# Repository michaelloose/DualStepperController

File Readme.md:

Stepper Controller
==================

Dieses Projekt entstand als kleines Nebenprojekt im Rahmen meiner Masterarbeit und soll eine performante und einfach anzusteuernde Möglichkeit bieten zwei Schrittmotoren mithilfe eines Schrittmotortreibers wie dem DM542 zu betreiben.

||
|:-------------------------------------------------:|:---------------------------------------------------------:
|Bestückte Leiterplatte                             |Beispielhafter Aufbau                                                    

## Befehlsübersicht

Die Übertragung findet
über einen mittels USB-CDC emulierten COM-Port statt. Aus diesem
Grund sind sämtliche Einstellungen zu Baudrate, Daten/Stopbits oder
Paritätsbits hinfällig. Der Controller unterscheidet bei den Befehlen
nicht zwischen Groß- und Kleinschreibung. Das Ende eines Befehles wird
durch ein Carriage Return `<CR> Hex:0x0D` signalisiert. Alternativ wird
auch ein Line Feed `<LF> Hex:0x0A` akzeptiert. Ein Befehl darf eine
maximale Länge von zwölf ASCII-Zeichen zuzüglich des Terminatorzeichens
aufweisen. Wird diese Länge überschritten, so wird das dreizehnte
Zeichen unabhängig vom Inhalt aus Terminator gewertet.\
Zum Testen des Controllers wird eine serielle Konsole benötigt. Dazu
eignet sich die Software *hTerm*, welche sowohl unter Windows
als auch unter Linux ausgeführt werden kann. Um den Motortreiber in eine
Softwareumgebung einzubinden, wurde eine
Treiberklasse in Python entwickelt, die es einem ermöglicht
Steuerbefehle auf einem hohen Level zu senden. Zusätzlich zu dieser
Treiberklasse existiert ebenfalls eine GUI um die Antriebe komfortabel manuell
verfahren zu können.

### Allgemeine Befehle

  |Name               |Befehl     |Erklärung
  |-------------------|-----------|-----------------------------------------------------------------------------------------------------------------------------------------------------
  |Reset              |`RST<cr>`  |Neustart des Controllers. Trennt ebenfalls die USB-Verbindung.
  |Halt               |`HLT<cr>`  |Anhalten aller Antriebe. Neue Befehle werden akzeptiert, Spulen sind weiterhin bestromt.
  |Not-Halt           |`EST<cr>`  |Anhalten aller Antriebe. Neue Befehle werden nicht mehr akzeptiert, Spulenstrom wird abgeschaltet, somit können die Antriebe von Hand bewegt werden
  |Freigabe Not-Halt  |`ESR<cr>`  |Rücksetzen des Not-Halt Zustandes. Spulenstrom wird aktiviert und neue Befehle akzeptiert.

### Steuerbefehle

#### Steuerbefehle an den Controller
 | Byte    |Erlaubte Werte                                | Erklärung
 | ------- |----------------------------------------------| -------------------------------------------------
 | 1       |`A` Antrieb A (Hier Drehtisch)                | Antrieb
 |         |`B` Antrieb B (Hier Linearantrieb)            | 
 | 2       |`P` Position                                  | Art des Befehls
 |         |`S` Geschwindigkeit                           | 
 |         |`H` Anhalten (Setzt Sollwert gleich Istwert)  | 
 |         |`Z` Soll- und Istwert auf 0 setzen            | 
 |         |`R` Referenzfahrt                             | 
 | 3       |`=` Zuweisung                                 | Zuweisung oder Abfrage
 |         |`?` Abfrage                                   | 
 | 4\...   |`<Wert>` Punkt als Dezimalseparator           | Nur für Setzen von Position und Geschwindigkeit
 | N       |`<CR>` Carriage Return                        | Ende eines Befehls

#### Antwort vom Controller

  |Byte   |Erlaubte Werte                             |Erklärung
  |-------|-------------------------------------------|-------------------------------------
  |1..2   |Byte 1 u. 2 des Befehls                    |Wiederholen des empfangenen Befehls
  |3      |`!` Ausführung Abgeschlossen               |Art der Antwort
  |       |`=` Befehl Empfangen, Antwort auf Anfrage  |
  |4\...  |`<Wert>` Punkt als Dezimalseparator        |Wert als Antwort einer Anfrage
  |N      |`<CR>` Carriage Return                     |Ende eines Befehls

### Parametrierbefehle

Um den Controller zu parametrieren muss dieser zunächst mittels des
Befehls `PARAM` in den Parametriermodus gebracht werden. Der Controller
quittiert diesen Modus mit der Ausgabe `PARAM`. In diesem Modus können
die Antriebe nicht verfahren werden. Wird dennoch ein Verfahrbefehl
gesendet, so wird dieser nicht ausgeführt und der Controller antwortet
wie bei einem ungültigen Befehl mit `?`. Der Parametriermodus kann mit
dem Befehl `EXIT` wieder beendet werden. Das Verlassen der
Parametriermodus wird vom Controller mit `OK` Quittiert. Der Controller antwortet auf
Parametrierbefehle in der selben Weise wie auf Steuerbefehle.\

  |Byte    |Erlaubte Werte                          | Erklärung
  |--------|----------------------------------------| ------------------------------------
  |1       |`A` Antrieb A                           | Antrieb
  |        |`B` Antrieb B                           |
  |2\...4  |`SPU`                                   | Schritte pro Einheit
  |        |`VLM`                                   | Geschwindigkeitsbegrenzung \[1,0\]
  |        |`VMX`                                   | Maximale Geschwindigkeit
  |        |`VDF`                                   | Standardgeschwindigkeit
  |        |`PLM`                                   | Positionssbegrenzung \[1,0\]
  |        |`PMX`                                   | Maximale Position
  |        |`PMN`                                   | Minimale Position
  |        |`ROF`                                   | Offset vom Referenzpunkt
  |        |`DIN`                                   | Richtungsumkehrung \[1,0\]
  |        |`RPL`                                   | Polarität Referenzschalter \[1,0\]
  |        |                                        | 0: Öffner, 1: Schließer
  |5       |`=` Zuweisung                           | Zuweisung oder Abfrage
  |        |`?` Abfrage                             | 
  |6\...   |**\<Wert>** Punkt als Dezimalseparator  | 
  |N       |**\<CR>** Carriage Return               | Ende eines Befehls

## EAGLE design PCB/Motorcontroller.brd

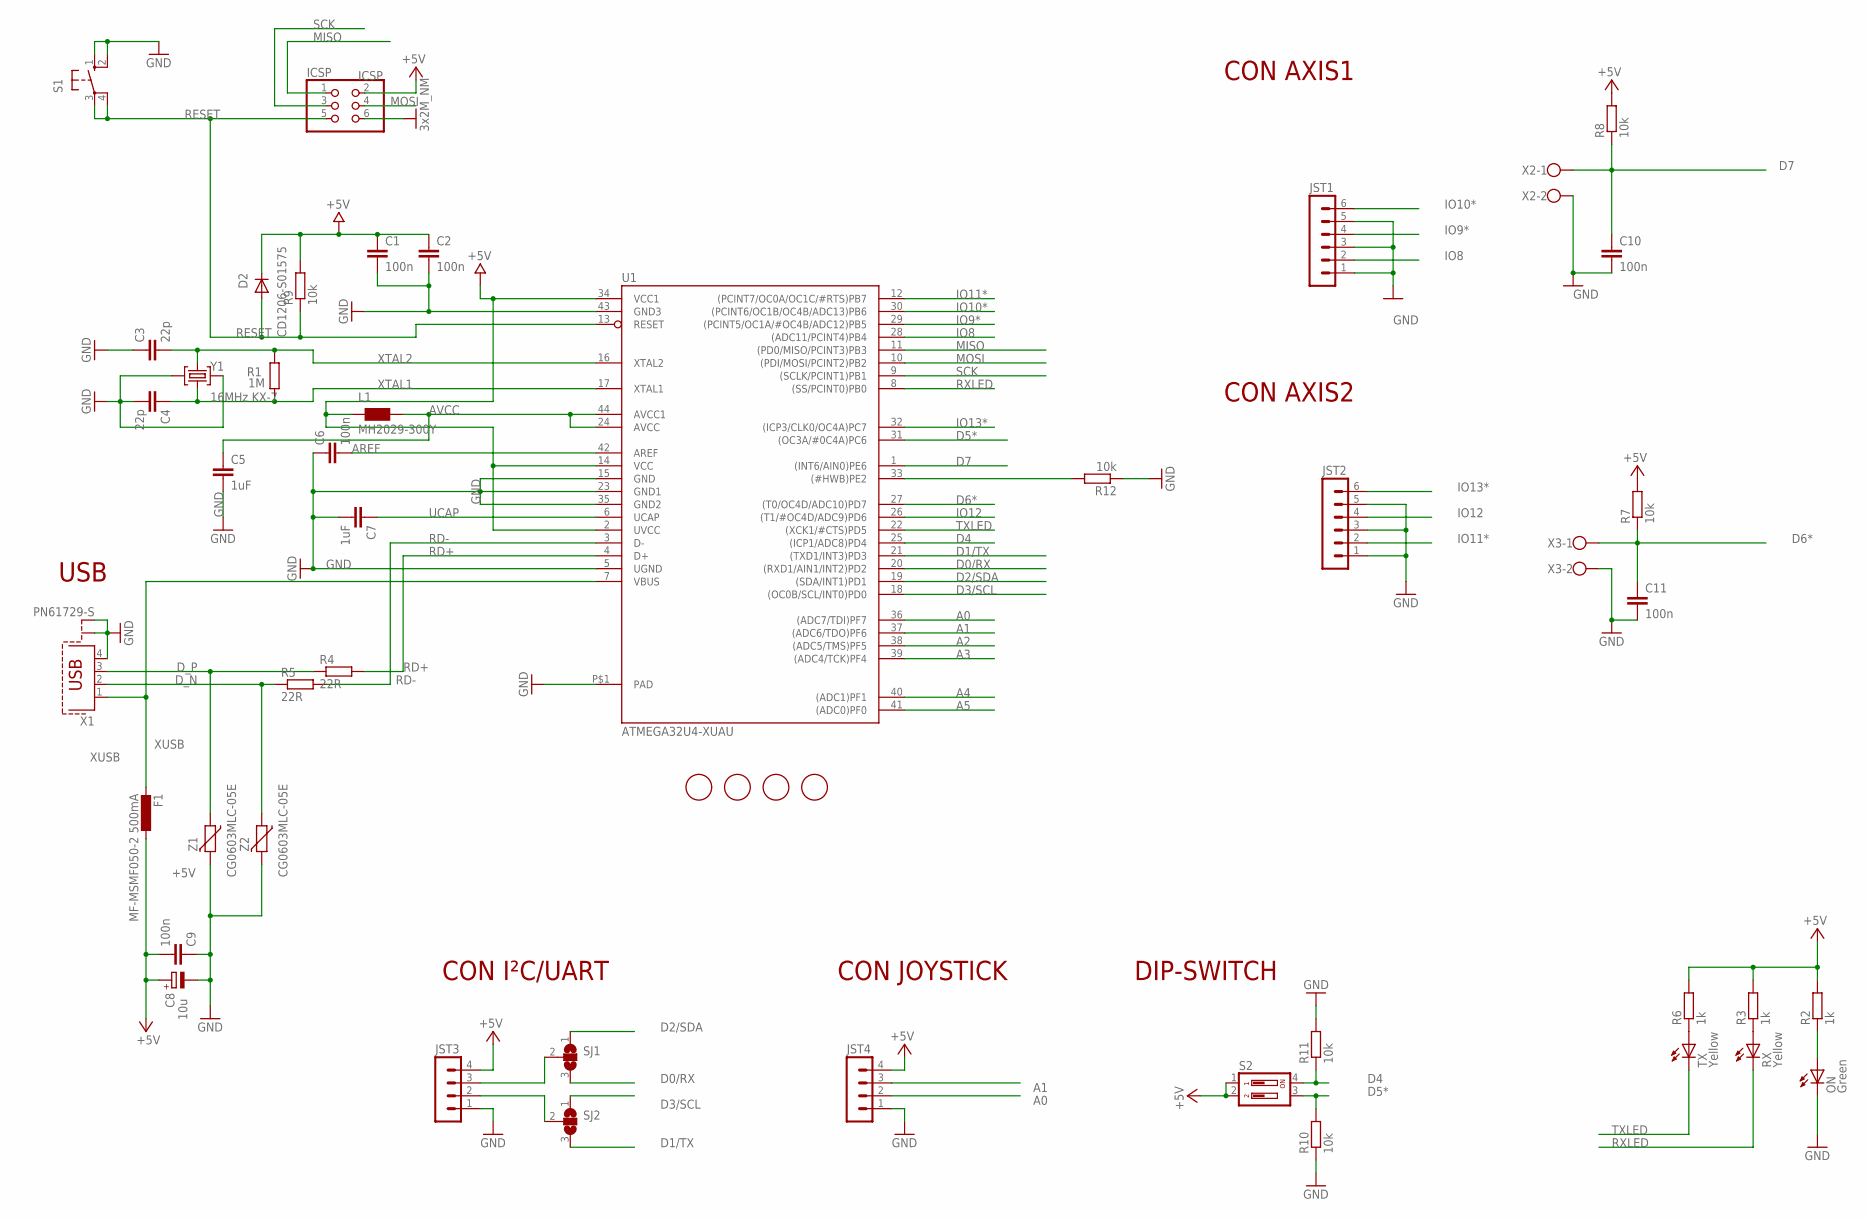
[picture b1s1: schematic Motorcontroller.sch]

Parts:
C1, C2, C6, C9, C10, C11: 100n; C0805
C3, C4: 22p; C0805
C5, C7: 1uF; C0805
C8: 10u; SMC_B
D2: CD1206-S01575; MINIMELF
F1: MF-MSMF050-2 500mA; L1812
FID1, FID2, FID3, FID4: FIDUCIALMOUNT; FIDUCIA-MOUNT
ICSP: ICSP; 2X03
JST1, JST2: MA06-1
JST3, JST4: MA04-1
L1: MH2029-300Y; 0805
ON: Green; CHIPLED_0805
R1: 1M; R0805
R2, R3, R6: 1k; R0805
R4, R5: 22R; R0805
R7, R8, R9, R10, R11, R12: 10k; R0805
RX: Yellow; CHIPLED_0805
S1: 10-XX; B3F-10XX
S2: DIP02YL
SJ1, SJ2: SJ2W; SJ_2
TX: Yellow; CHIPLED_0805
U1: ATMEGA32U4-XUAU; TQFP44-PAD
X1: PN61729-S
X2, X3: W237-102
Y1: 16MHz KX-7; CRYSTAL-3.2-2.5
Z1, Z2: CG0603MLC-05E; CT/CN0805

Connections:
+5V: C1.1, C2.1, C8.+, C9.2, D2.C, F1.1, ICSP.2, JST3.4, JST4.4, L1.1, R2.2, R3.2, R6.2, R7.2, R8.2, R9.2, S2.1, S2.2, U1.2 (UVCC), U1.14 (VCC), U1.34 (VCC1)
A0: JST4.2, U1.36 ((ADC7/TDI)PF7)
A1: JST4.3, U1.37 ((ADC6/TDO)PF6)
A2: U1.38 ((ADC5/TMS)PF5)
A3: U1.39 ((ADC4/TCK)PF4)
A4: U1.40 ((ADC1)PF1)
A5: U1.41 ((ADC0)PF0)
AREF: C6.2, U1.42 (AREF)
AVCC: C5.1, L1.2, U1.24 (AVCC), U1.44 (AVCC1)
D0/RX: SJ1.3, U1.20 ((RXD1/AIN1/INT2)PD2)
D1/TX: SJ2.3, U1.21 ((TXD1/INT3)PD3)
D2/SDA: SJ1.1, U1.19 ((SDA/INT1)PD1)
D3/SCL: SJ2.1, U1.18 ((OC0B/SCL/INT0)PD0)
D4: R11.1, S2.4, U1.25 ((ICP1/ADC8)PD4)
D5*: R10.2, S2.3, U1.31 ((OC3A/#0C4A)PC6)
D6*: C11.1, R7.1, U1.27 ((T0/OC4D/ADC10)PD7), X3.1
D7: C10.1, R8.1, U1.1 ((INT6/AIN0)PE6), X2.1
D_N: R5.1, X1.2, Z2.1
D_P: R4.1, X1.3, Z1.1
GND: C1.2, C2.2, C3.1, C4.2, C5.2, C6.1, C7.2, C8.-, C9.1, C10.2, C11.2, ICSP.6, JST1.1, JST1.3, JST1.5, JST2.1, JST2.3, JST2.5, JST3.1, JST4.1, ON.C, R10.1, R11.2, R12.1, S1.1 (S), S1.2 (S1), U1.5 (UGND), U1.15 (GND), U1.23 (GND1), U1.35 (GND2), U1.43 (GND3), U1.P$1 (PAD), X1.4, X1.S1, X1.S2, X2.2, X3.2, Y1.2 (GND), Y1.4 (GND), Z1.2, Z2.2
IO8: JST1.2, U1.28 ((ADC11/PCINT4)PB4)
IO9*: JST1.4, U1.29 ((PCINT5/OC1A/#OC4B/ADC12)PB5)
IO10*: JST1.6, U1.30 ((PCINT6/OC1B/OC4B/ADC13)PB6)
IO11*: JST2.2, U1.12 ((PCINT7/OC0A/OC1C/#RTS)PB7)
IO12: JST2.4, U1.26 ((T1/#OC4D/ADC9)PD6)
IO13*: JST2.6, U1.32 ((ICP3/CLK0/OC4A)PC7)
MISO: ICSP.1, U1.11 ((PD0/MISO/PCINT3)PB3)
MOSI: ICSP.4, U1.10 ((PDI/MOSI/PCINT2)PB2)
unnamed: R3.1, RX.A
unnamed: R6.1, TX.A
unnamed: ON.A, R2.1
unnamed: JST3.3, SJ1.2
unnamed: JST3.2, SJ2.2
unnamed: R12.2, U1.33 ((#HWB)PE2)
RD+: R4.2, U1.4 (D+)
RD-: R5.2, U1.3 (D-)
RESET: D2.A, ICSP.5, R9.1, S1.3, S1.4 (P1), U1.13 (RESET)
RXLED: RX.C, U1.8 ((SS/PCINT0)PB0)
SCK: ICSP.3, U1.9 ((SCLK/PCINT1)PB1)
TXLED: TX.C, U1.22 ((XCK1/#CTS)PD5)
UCAP: C7.1, U1.6 (UCAP)
XTAL1: C4.1, R1.1, U1.17 (XTAL1), Y1.1 (C1)
XTAL2: C3.2, R1.2, U1.16 (XTAL2), Y1.3 (C2)
XUSB: F1.2, U1.7 (VBUS), X1.1

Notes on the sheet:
USB
CON I²C/UART
CON JOYSTICK
DIP-SWITCH
CON AXIS1
CON AXIS2

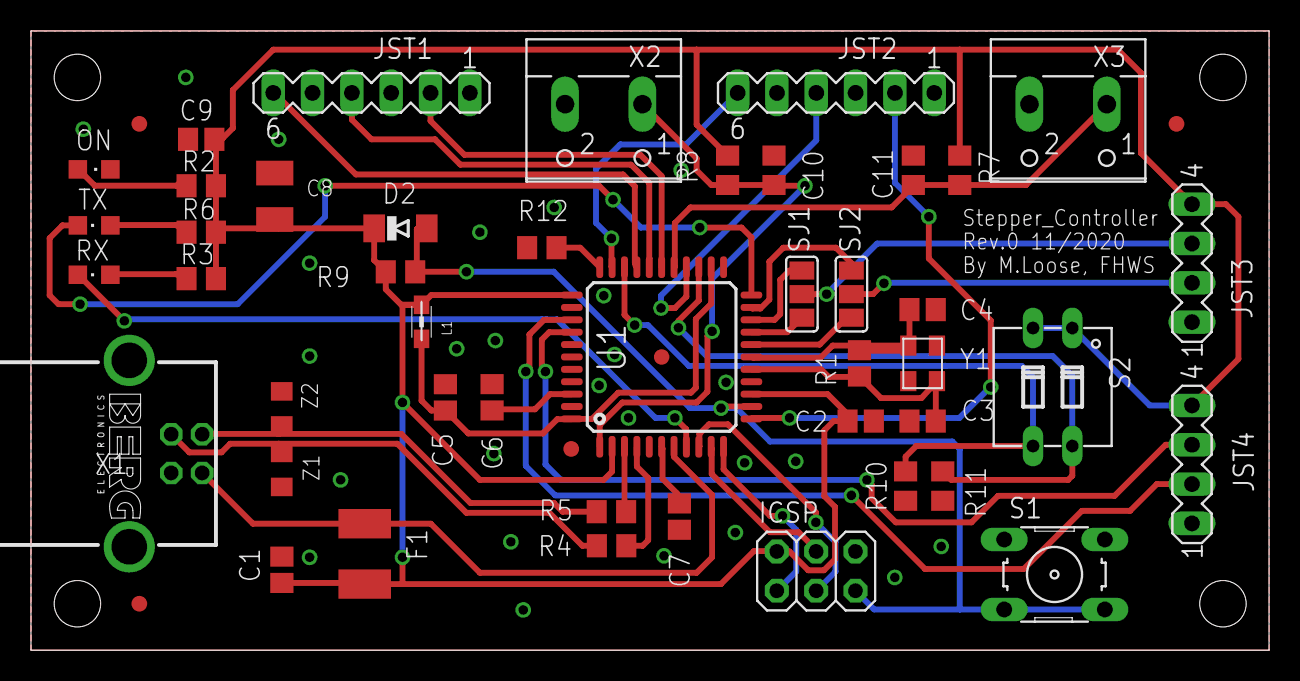
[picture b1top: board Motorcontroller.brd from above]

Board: 2 copper layers, 80.0 x 40.0 mm, 49 parts (0 on the bottom side), 40 nets.

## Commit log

2020-12-08 Added License File
2020-12-15 Changed Pinmap to fit to new Board
2021-08-03 Porting Code to C and fitting to use LUFA Library
2021-08-03 Fixing Bug with drives not accepting direction inverse commands when in motion
2021-08-04 Enhancing Speed Accuracy
2021-08-09 Updating Documentation
2021-08-09 Updating Readme
2021-09-17 Minor Fixes
2021-09-27 Added Demo GUI
